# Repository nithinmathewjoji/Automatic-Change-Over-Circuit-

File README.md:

# Automatic-Change-Over-Circuit-
Automatic Change Over Circuit with complete project file and gerb file (made using ki cad) this device is helpful to switch between 2 dc power source according to their availability

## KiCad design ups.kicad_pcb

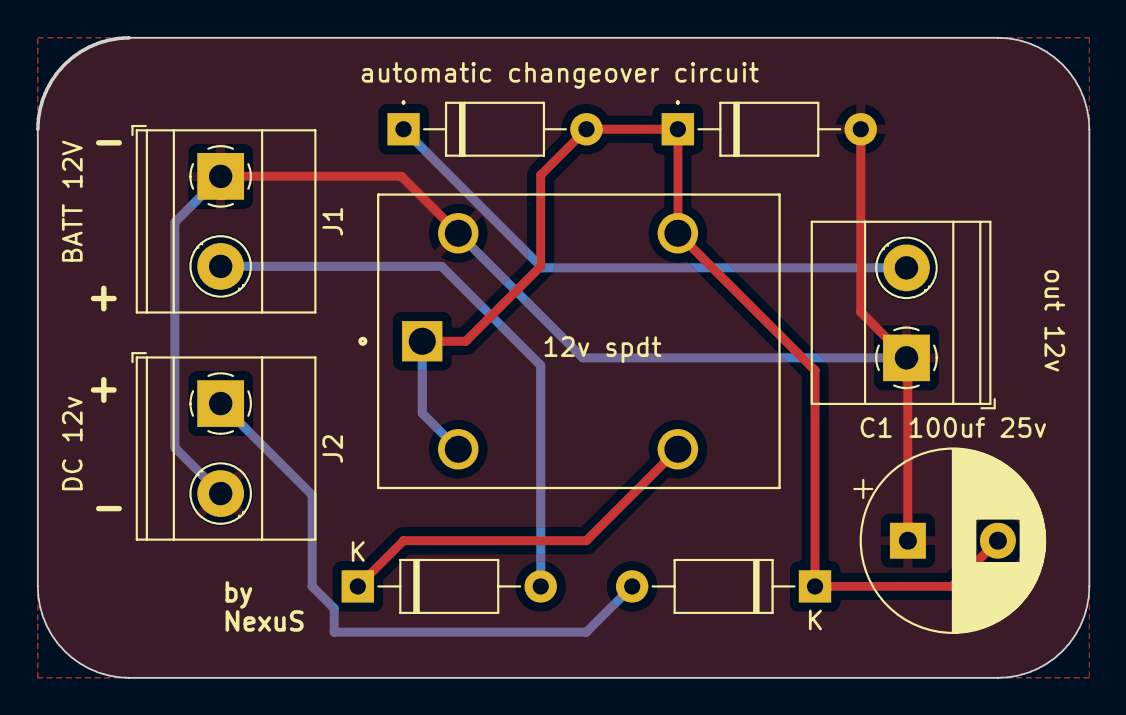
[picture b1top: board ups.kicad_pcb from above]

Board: 2 copper layers, 58.4 x 35.6 mm, 9 parts (0 on the bottom side), 6 nets.

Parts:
C1 100uf 25v: C; CP_Radial_D10.0mm_P5.00mm
D1, D2, D3, D4: D; D_A-405_P10.16mm_Horizontal
J1, J2, J3: Screw_Terminal_01x02; TerminalBlock_Phoenix_MKDS-1,5-2_1x02_P5.00mm_Horizontal
K1: JS1-12V-F; RELAY_JS1-12V-F

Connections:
GND: C1 100uf 25v.1, D2.2 (A), J1.1, J2.2, J3.1, K1.5
unnamed: C1 100uf 25v.2, D1.2 (A), D2.1 (K), D4.1 (K), K1.1, K1.2, K1.4
unnamed: D1.1 (K), J3.2
unnamed: D3.2 (A), J1.2
unnamed: D3.1 (K), K1.3
unnamed: D4.2 (A), J2.1

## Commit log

2024-02-21 added files via upoad
